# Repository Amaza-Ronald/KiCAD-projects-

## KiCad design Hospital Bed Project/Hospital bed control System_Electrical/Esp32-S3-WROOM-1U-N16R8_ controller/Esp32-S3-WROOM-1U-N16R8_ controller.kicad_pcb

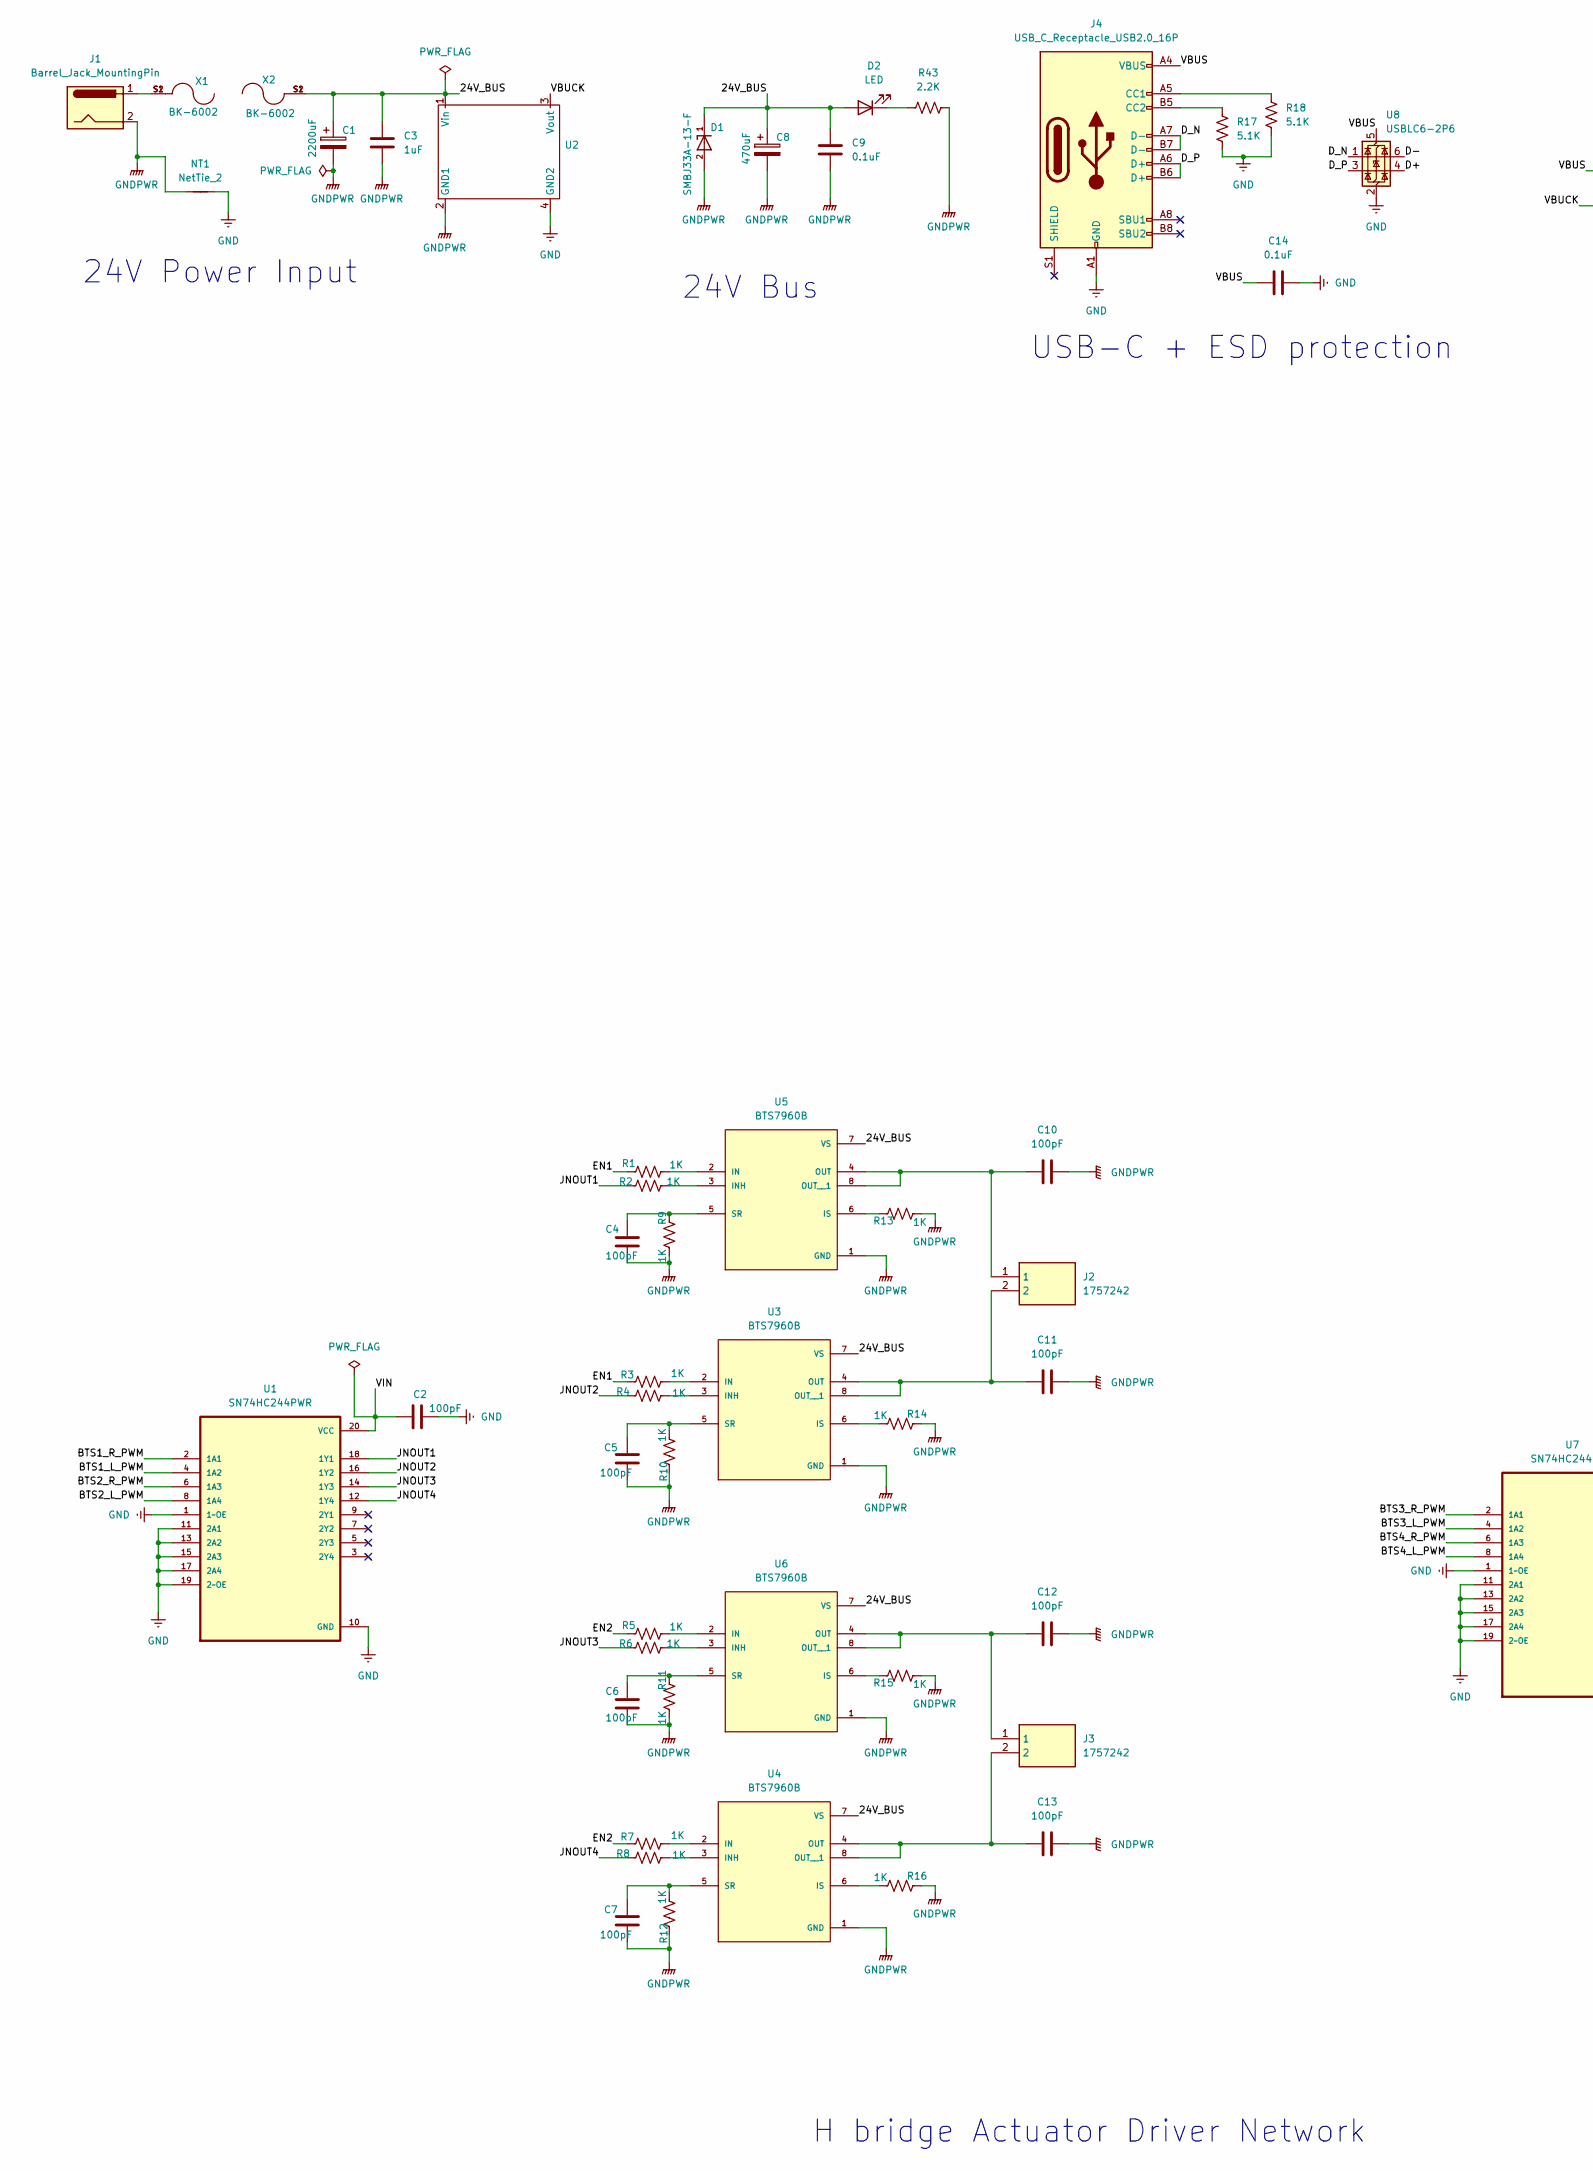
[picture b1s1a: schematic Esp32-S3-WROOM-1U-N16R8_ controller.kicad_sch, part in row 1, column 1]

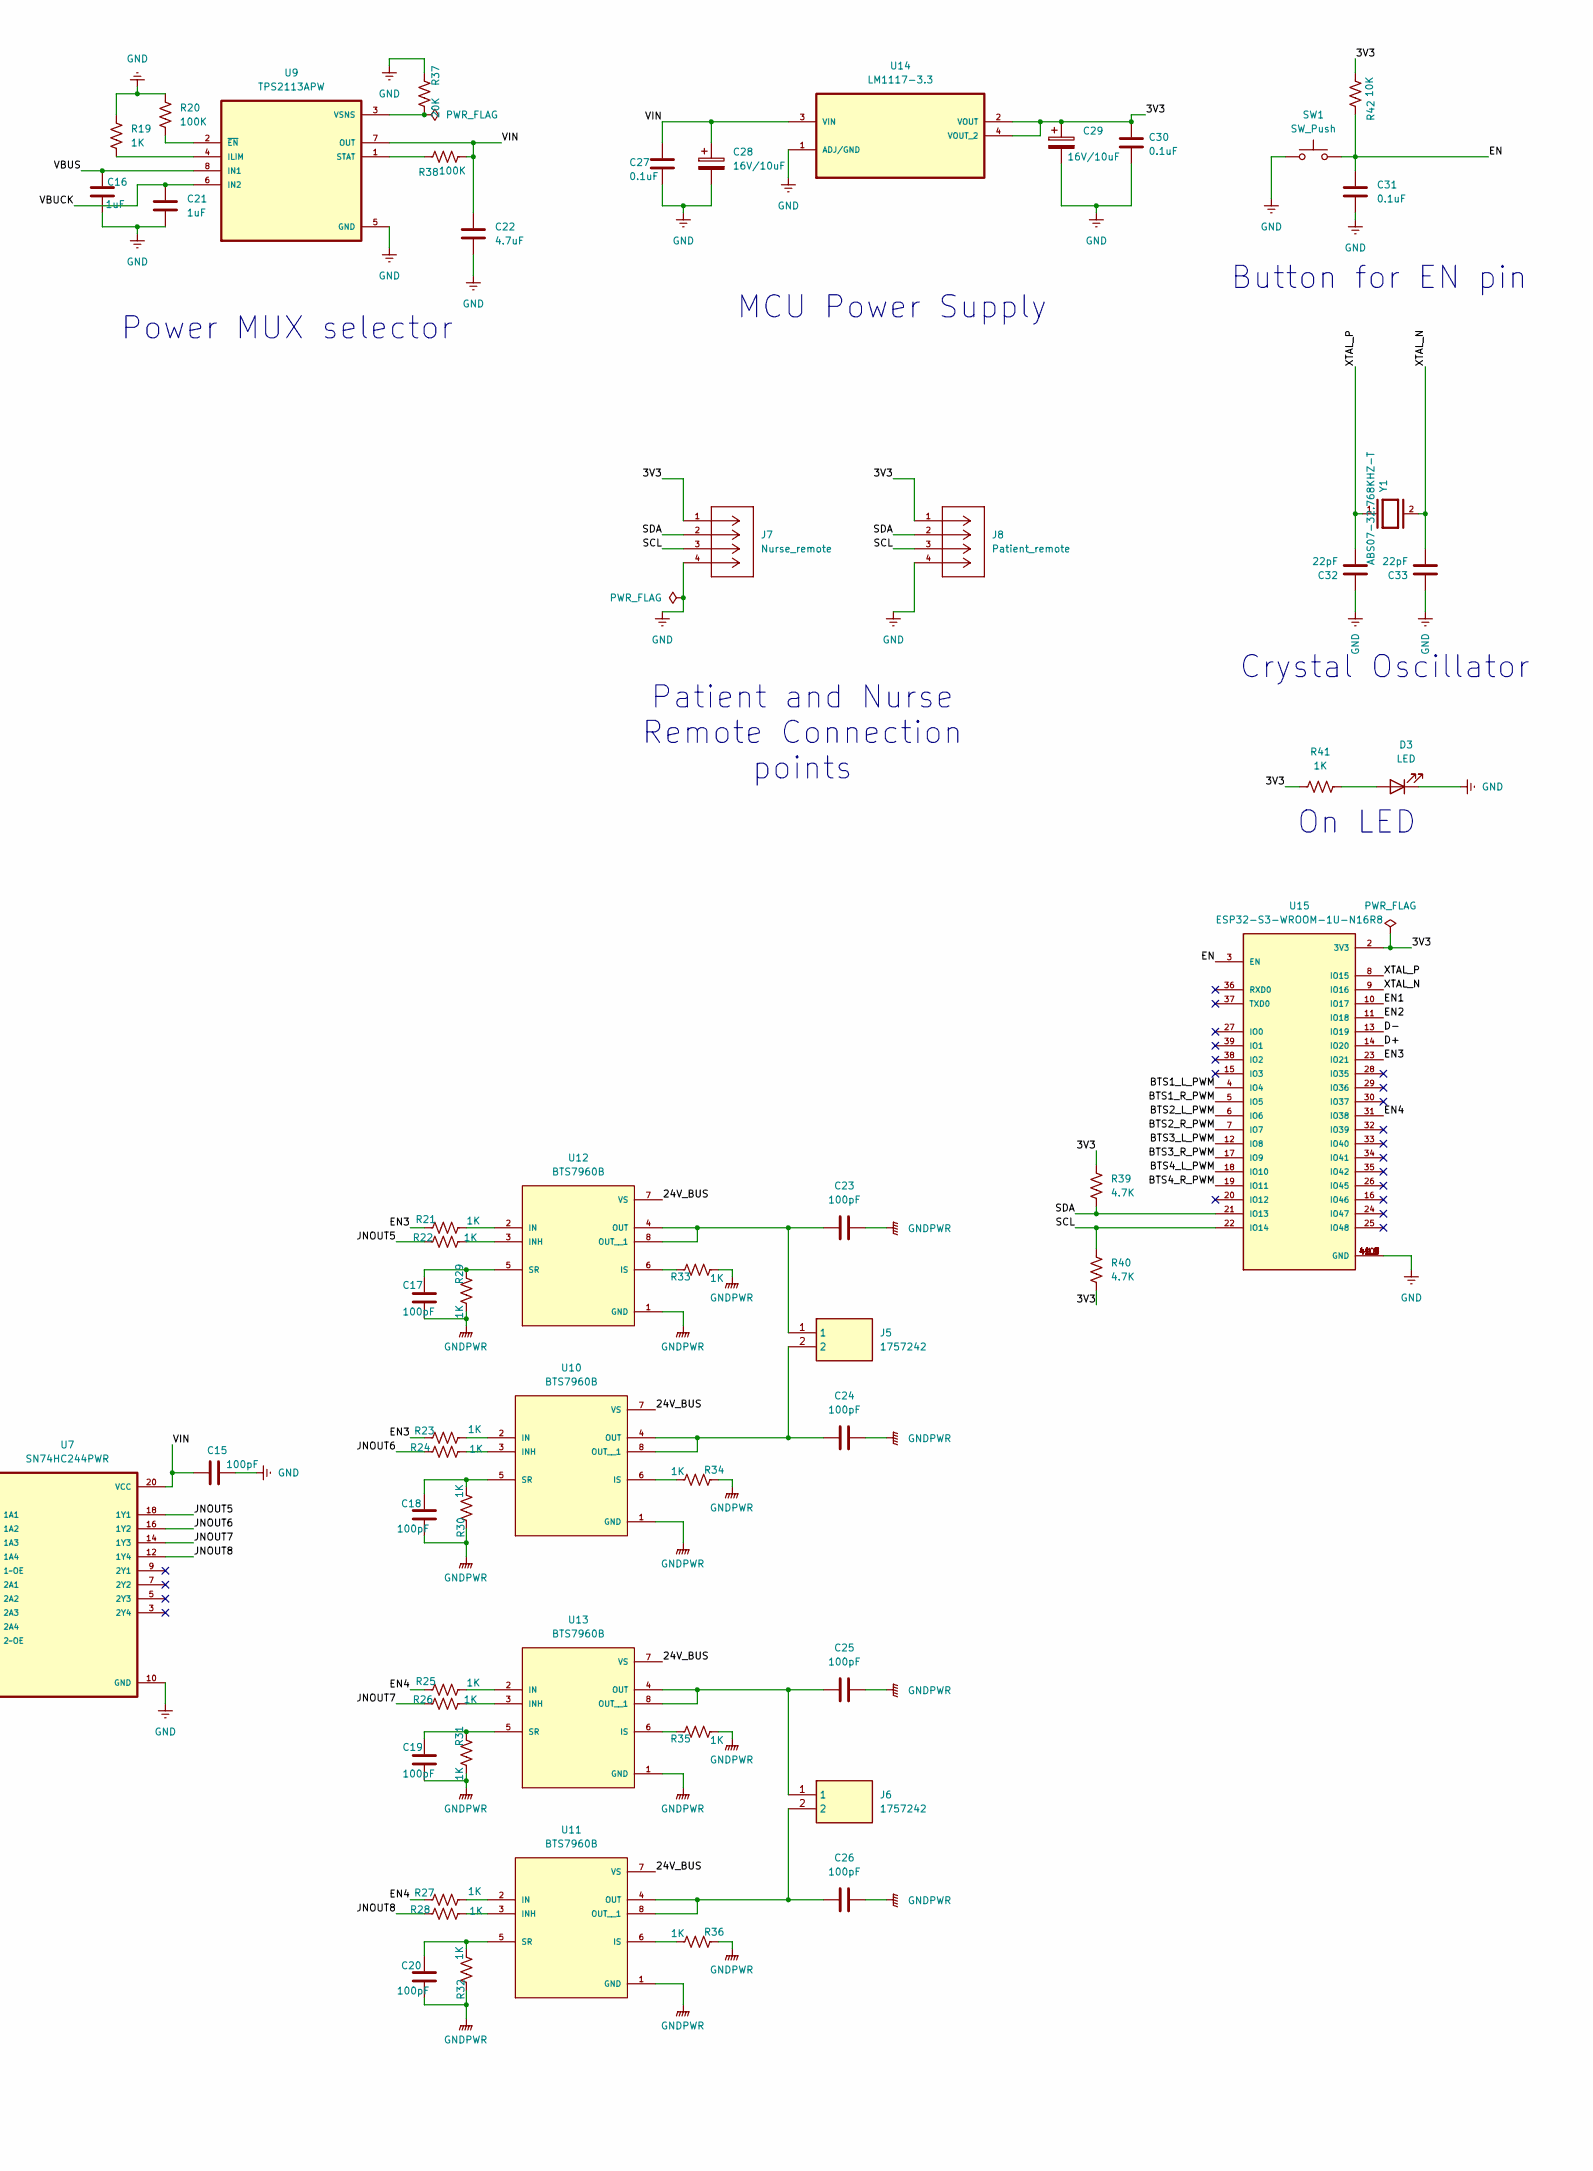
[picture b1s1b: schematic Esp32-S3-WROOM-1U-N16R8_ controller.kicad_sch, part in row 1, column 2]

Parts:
C1: 2200uF; CP_Radial_D16.0mm_P7.50mm
C2, C4, C5, C6, C7, C10, C11, C12, C13, C15, C17, C18, C19, C20, C23, C24, C25, C26: 100pF; C_0603_1608Metric
C3, C16, C21: 1uF; C_0603_1608Metric; MANUFACTURER_PART_NUMBER MAJCU168BB7104KTEA01
C8: 470uF; CP_Elec_10x10.5
C9, C14, C27, C30, C31: 0.1uF; C_0603_1608Metric; MANUFACTURER_PART_NUMBER MAJCU168BB7104KTEA01
C22: 4.7uF; C_0603_1608Metric; MANUFACTURER_PART_NUMBER 06036C475KAT2A
C28, C29: 16V/10uF; CP_Elec_4x5.4
C32, C33: 22pF; C_0603_1608Metric
D1: SMBJ33A-13-F; DIOM5336X250N; PARTREV 20 - 2
D2: LED; LED_D3.0mm
D3: LED; LED_1206_3216Metric
J1: Barrel_Jack_MountingPin; BarrelJack_GCT_DCJ200-10-A_Horizontal
J2, J3, J5, J6: 1757242; CONN_395224002_MOL; Mouser Part Number 651-1757242
J4: USB_C_Receptacle_USB2.0_16P; USB_C_Receptacle_GCT_USB4105-xx-A_16P_TopMnt_Horizontal
J7: Nurse_remote; CONN04_1718560004_MOL; MANUFACTURER_PART_NUMBER 1718560004
J8: Patient_remote; CONN04_1718560004_MOL; MANUFACTURER_PART_NUMBER 1718560004
NT1: NetTie_2; NetTie-2_SMD_Pad2.0mm
R1, R2, R3, R4, R5, R6, R7, R8, R9, R10, R11, R12, R13, R14, R15, R16, R19, R21, R22, R23, R24, R25, R26, R27, R28, R29, R30, R31, R32, R33, R34, R35, R36, R41: 1K; R_0603_1608Metric
R17, R18: 5.1K; R_0603_1608Metric
R20, R38: 100K; R_0603_1608Metric
R37: 20K; R_0603_1608Metric
R39, R40: 4.7K; R_0603_1608Metric
R42: 10K; R_0603_1608Metric
R43: 2.2K; R_0603_1608Metric
SW1: SW_Push; SW_SPST_FSMSM
U1, U7: SN74HC244PWR; SOP65P640X120-20N
U2: XL1509 DC-DC Step Down Buck Power Supply Module
U3, U4, U5, U6, U10, U11, U12, U13: BTS7960B; DPAK127P1490X440-8N; PARTREV 1.1
U8: USBLC6-2P6; SOT-666
U9: TPS2113APW; SOP65P640X120-8N; DigiKey_Part_Number 296-34596-5-ND
U14: LM1117-3.3; SOT230
U15: ESP32-S3-WROOM-1U-N16R8; XCVR_ESP32-S3-WROOM-1U-N16R8; PARTREV v1.1
X1, X2: BK-6002; BAT_BK-6002; PARTREV A
Y1: ABS07-32.768KHZ-T; XTAL_ABS07-32.768KHZ-T; PARTREV 08.19.15

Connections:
/3V3: C29.1, C30.2, J7.1, J8.1, R39.2, R40.1, R41.1, R42.2, U14.2 (VOUT), U14.4 (VOUT_2), U15.2 (3V3)
/24V_BUS: C1.1, C3.2, C8.1, C9.2, D1.1, D2.2 (A), U2.1 (Vin), U3.7 (VS), U4.7 (VS), U5.7 (VS), U6.7 (VS), U10.7 (VS), U11.7 (VS), U12.7 (VS), U13.7 (VS), X2.S1, X2.S2
/BTS1_L_PWM: U1.4 (1A2), U15.4 (IO4)
/BTS1_R_PWM: U1.2 (1A1), U15.5 (IO5)
/BTS2_L_PWM: U1.8 (1A4), U15.6 (IO6)
/BTS2_R_PWM: U1.6 (1A3), U15.7 (IO7)
/BTS3_L_PWM: U7.4 (1A2), U15.12 (IO8)
/BTS3_R_PWM: U7.2 (1A1), U15.17 (IO9)
/BTS4_L_PWM: U7.8 (1A4), U15.18 (IO10)
/BTS4_R_PWM: U7.6 (1A3), U15.19 (IO11)
/D+: U8.4 (I/O2), U15.14 (IO20)
/D-: U8.6 (I/O1), U15.13 (IO19)
/D_N: J4.A7 (D-), J4.B7 (D-), U8.1 (I/O1)
/D_P: J4.A6 (D+), J4.B6 (D+), U8.3 (I/O2)
/EN: C31.1, R42.1, SW1.2, U15.3 (EN)
/EN1: R1.1, R3.1, U15.10 (IO17)
/EN2: R5.1, R7.1, U15.11 (IO18)
/EN3: R21.1, R23.1, U15.23 (IO21)
/EN4: R25.1, R27.1, U15.31 (IO38)
/JNOUT1: R2.1, U1.18 (1Y1)
/JNOUT2: R4.1, U1.16 (1Y2)
/JNOUT3: R6.1, U1.14 (1Y3)
/JNOUT4: R8.1, U1.12 (1Y4)
/JNOUT5: R22.1, U7.18 (1Y1)
/JNOUT6: R24.1, U7.16 (1Y2)
/JNOUT7: R26.1, U7.14 (1Y3)
/JNOUT8: R28.1, U7.12 (1Y4)
/SCL: J7.3, J8.3, R40.2, U15.22 (IO14)
/SDA: J7.2, J8.2, R39.1, U15.21 (IO13)
/VBUCK: C21.2, U2.3 (Vout), U9.6 (IN2)
/VBUS: C14.1, C16.2, J4.A4 (VBUS), J4.A9 (VBUS), J4.B4 (VBUS), J4.B9 (VBUS), U8.5 (VBUS), U9.8 (IN1)
/VIN: C2.2, C15.2, C22.2, C27.2, C28.1, R38.2, U1.20 (VCC), U7.20 (VCC), U9.7 (OUT), U14.3 (VIN)
/XTAL_N: C33.1, U15.9 (IO16), Y1.2
/XTAL_P: C32.1, U15.8 (IO15), Y1.1
GND: C2.1, C14.2, C15.1, C16.1, C21.1, C22.1, C27.1, C28.2, C29.2, C30.1, C31.2, C32.2, C33.2, D3.1 (K), J4.A1 (GND), J4.A12 (GND), J4.B1 (GND), J4.B12 (GND), J7.4, J8.4, NT1.2, R17.2, R18.2, R19.1, R20.1, R37.2, SW1.1, U1.1 (1~OE), U1.10 (GND), U1.11 (2A1), U1.13 (2A2), U1.15 (2A3), U1.17 (2A4), U1.19 (2~OE), U2.4 (GND2), U7.1 (1~OE), U7.10 (GND), U7.11 (2A1), U7.13 (2A2), U7.15 (2A3), U7.17 (2A4), U7.19 (2~OE), U8.2 (GND), U9.5 (GND), U14.1 (ADJ/GND), U15.1 (GND), U15.40 (GND), U15.41_1 (GND), U15.41_2 (GND), U15.41_3 (GND), U15.41_4 (GND), U15.41_5 (GND), U15.41_6 (GND), U15.41_7 (GND), U15.41_8 (GND), U15.41_9 (GND)
GNDPWR: C1.2, C3.1, C4.2, C5.2, C6.2, C7.2, C8.2, C9.1, C10.2, C11.2, C12.2, C13.2, C17.2, C18.2, C19.2, C20.2, C23.2, C24.2, C25.2, C26.2, D1.2, J1.2, NT1.1, R9.1, R10.1, R11.1, R12.1, R13.1, R14.2, R15.1, R16.2, R29.1, R30.1, R31.1, R32.1, R33.1, R34.2, R35.1, R36.2, R43.2, U2.2 (GND1), U3.1 (GND), U4.1 (GND), U5.1 (GND), U6.1 (GND), U10.1 (GND), U11.1 (GND), U12.1 (GND), U13.1 (GND)
unnamed: D2.1 (K), R43.1
unnamed: D3.2 (A), R41.2
unnamed: J1.1, X1.S1, X1.S2
unnamed: J4.A5 (CC1), R18.1
unnamed: J4.B5 (CC2), R17.1
unnamed: R3.2, U3.2 (IN)
unnamed: R4.2, U3.3 (INH)
unnamed: R14.1, U3.6 (IS)
unnamed: C11.1, J2.2, U3.4 (OUT), U3.8 (OUT__1)
unnamed: C5.1, R10.2, U3.5 (SR)
unnamed: R7.2, U4.2 (IN)
unnamed: R8.2, U4.3 (INH)
unnamed: R16.1, U4.6 (IS)
unnamed: C13.1, J3.2, U4.4 (OUT), U4.8 (OUT__1)
unnamed: C7.1, R12.2, U4.5 (SR)
unnamed: R1.2, U5.2 (IN)
unnamed: R2.2, U5.3 (INH)
unnamed: R13.2, U5.6 (IS)
unnamed: C10.1, J2.1, U5.4 (OUT), U5.8 (OUT__1)
unnamed: C4.1, R9.2, U5.5 (SR)
unnamed: R5.2, U6.2 (IN)
unnamed: R6.2, U6.3 (INH)
unnamed: R15.2, U6.6 (IS)
unnamed: C12.1, J3.1, U6.4 (OUT), U6.8 (OUT__1)
unnamed: C6.1, R11.2, U6.5 (SR)
unnamed: R19.2, U9.4 (ILIM)
unnamed: R38.1, U9.1 (STAT)
unnamed: R37.1, U9.3 (VSNS)
unnamed: R20.2, U9.2 (~EN)
unnamed: R23.2, U10.2 (IN)
unnamed: R24.2, U10.3 (INH)
unnamed: R34.1, U10.6 (IS)
unnamed: C24.1, J5.2, U10.4 (OUT), U10.8 (OUT__1)
unnamed: C18.1, R30.2, U10.5 (SR)
unnamed: R27.2, U11.2 (IN)
unnamed: R28.2, U11.3 (INH)
unnamed: R36.1, U11.6 (IS)
unnamed: C26.1, J6.2, U11.4 (OUT), U11.8 (OUT__1)
unnamed: C20.1, R32.2, U11.5 (SR)
unnamed: R21.2, U12.2 (IN)
unnamed: R22.2, U12.3 (INH)
unnamed: R33.2, U12.6 (IS)
unnamed: C23.1, J5.1, U12.4 (OUT), U12.8 (OUT__1)
unnamed: C17.1, R29.2, U12.5 (SR)
unnamed: R25.2, U13.2 (IN)
unnamed: R26.2, U13.3 (INH)
unnamed: R35.2, U13.6 (IS)
unnamed: C25.1, J6.1, U13.4 (OUT), U13.8 (OUT__1)
unnamed: C19.1, R31.2, U13.5 (SR)

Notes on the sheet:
H bridge Actuator Driver Network
Crystal Oscillator
MCU Power Supply
Power MUX selector
24V Bus
Button for EN pin
USB-C + ESD protection
24V Power Input
On LED
Patient and Nurse Remote Connection points

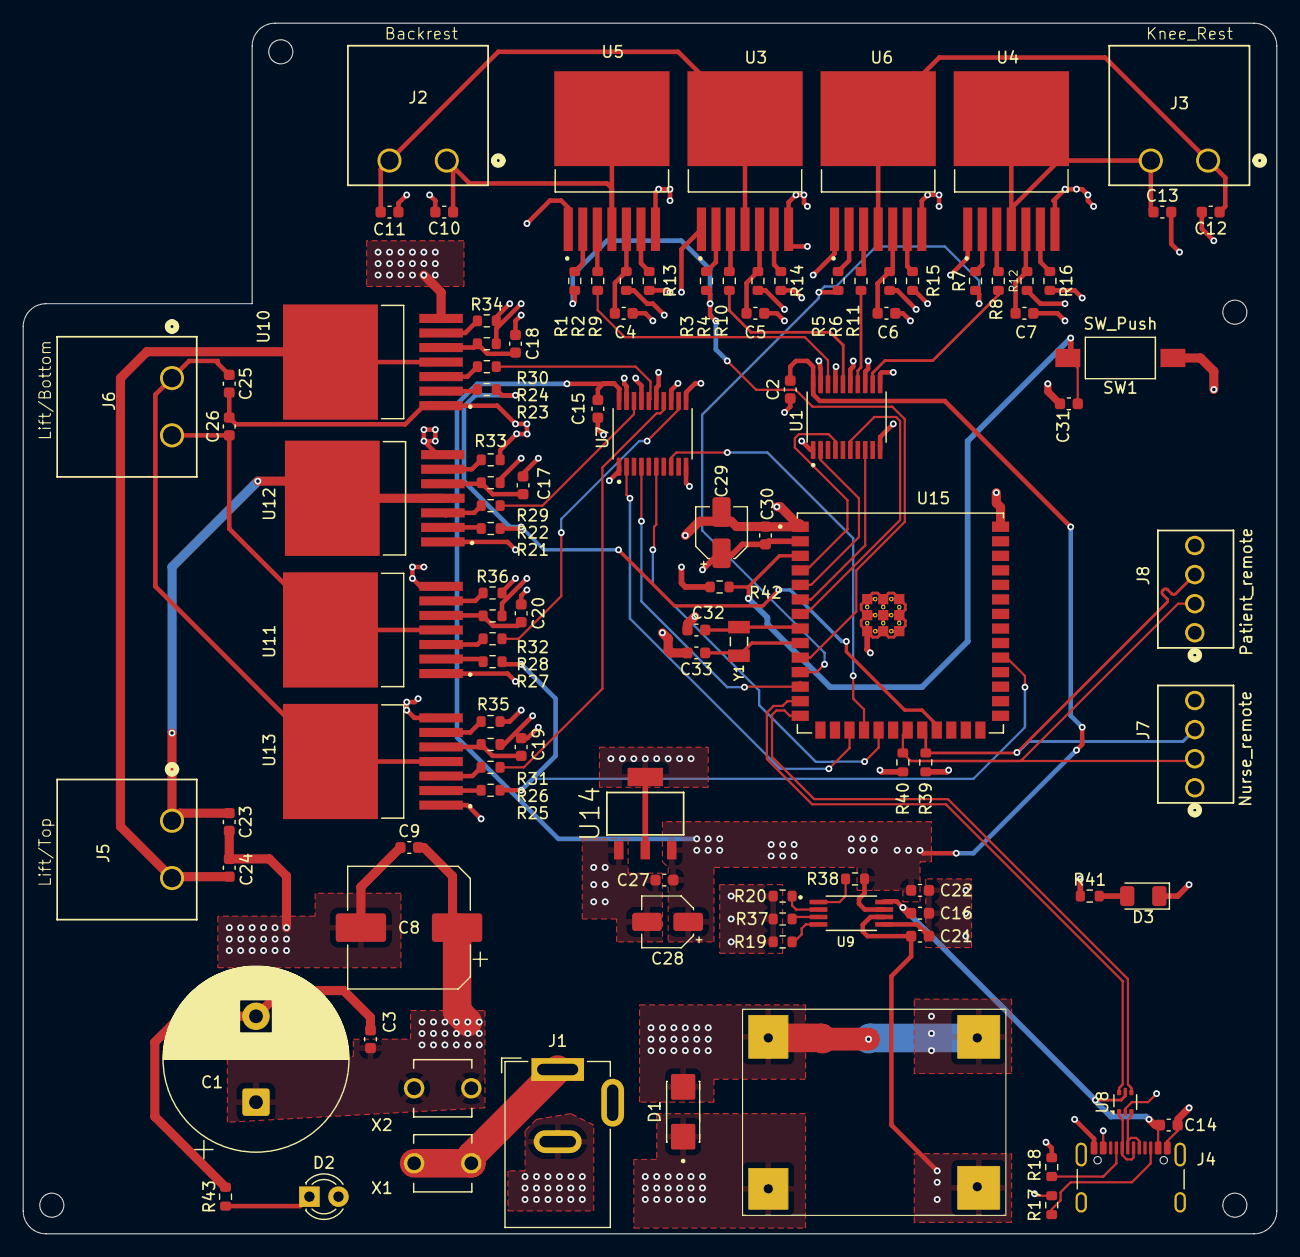
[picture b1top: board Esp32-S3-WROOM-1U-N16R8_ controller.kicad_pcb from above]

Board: 4 copper layers, 109.5 x 105.7 mm, 111 parts (0 on the bottom side), 85 nets.

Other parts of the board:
REF2, REF2#2, REF3, REF4: MountingHole_2.1mm

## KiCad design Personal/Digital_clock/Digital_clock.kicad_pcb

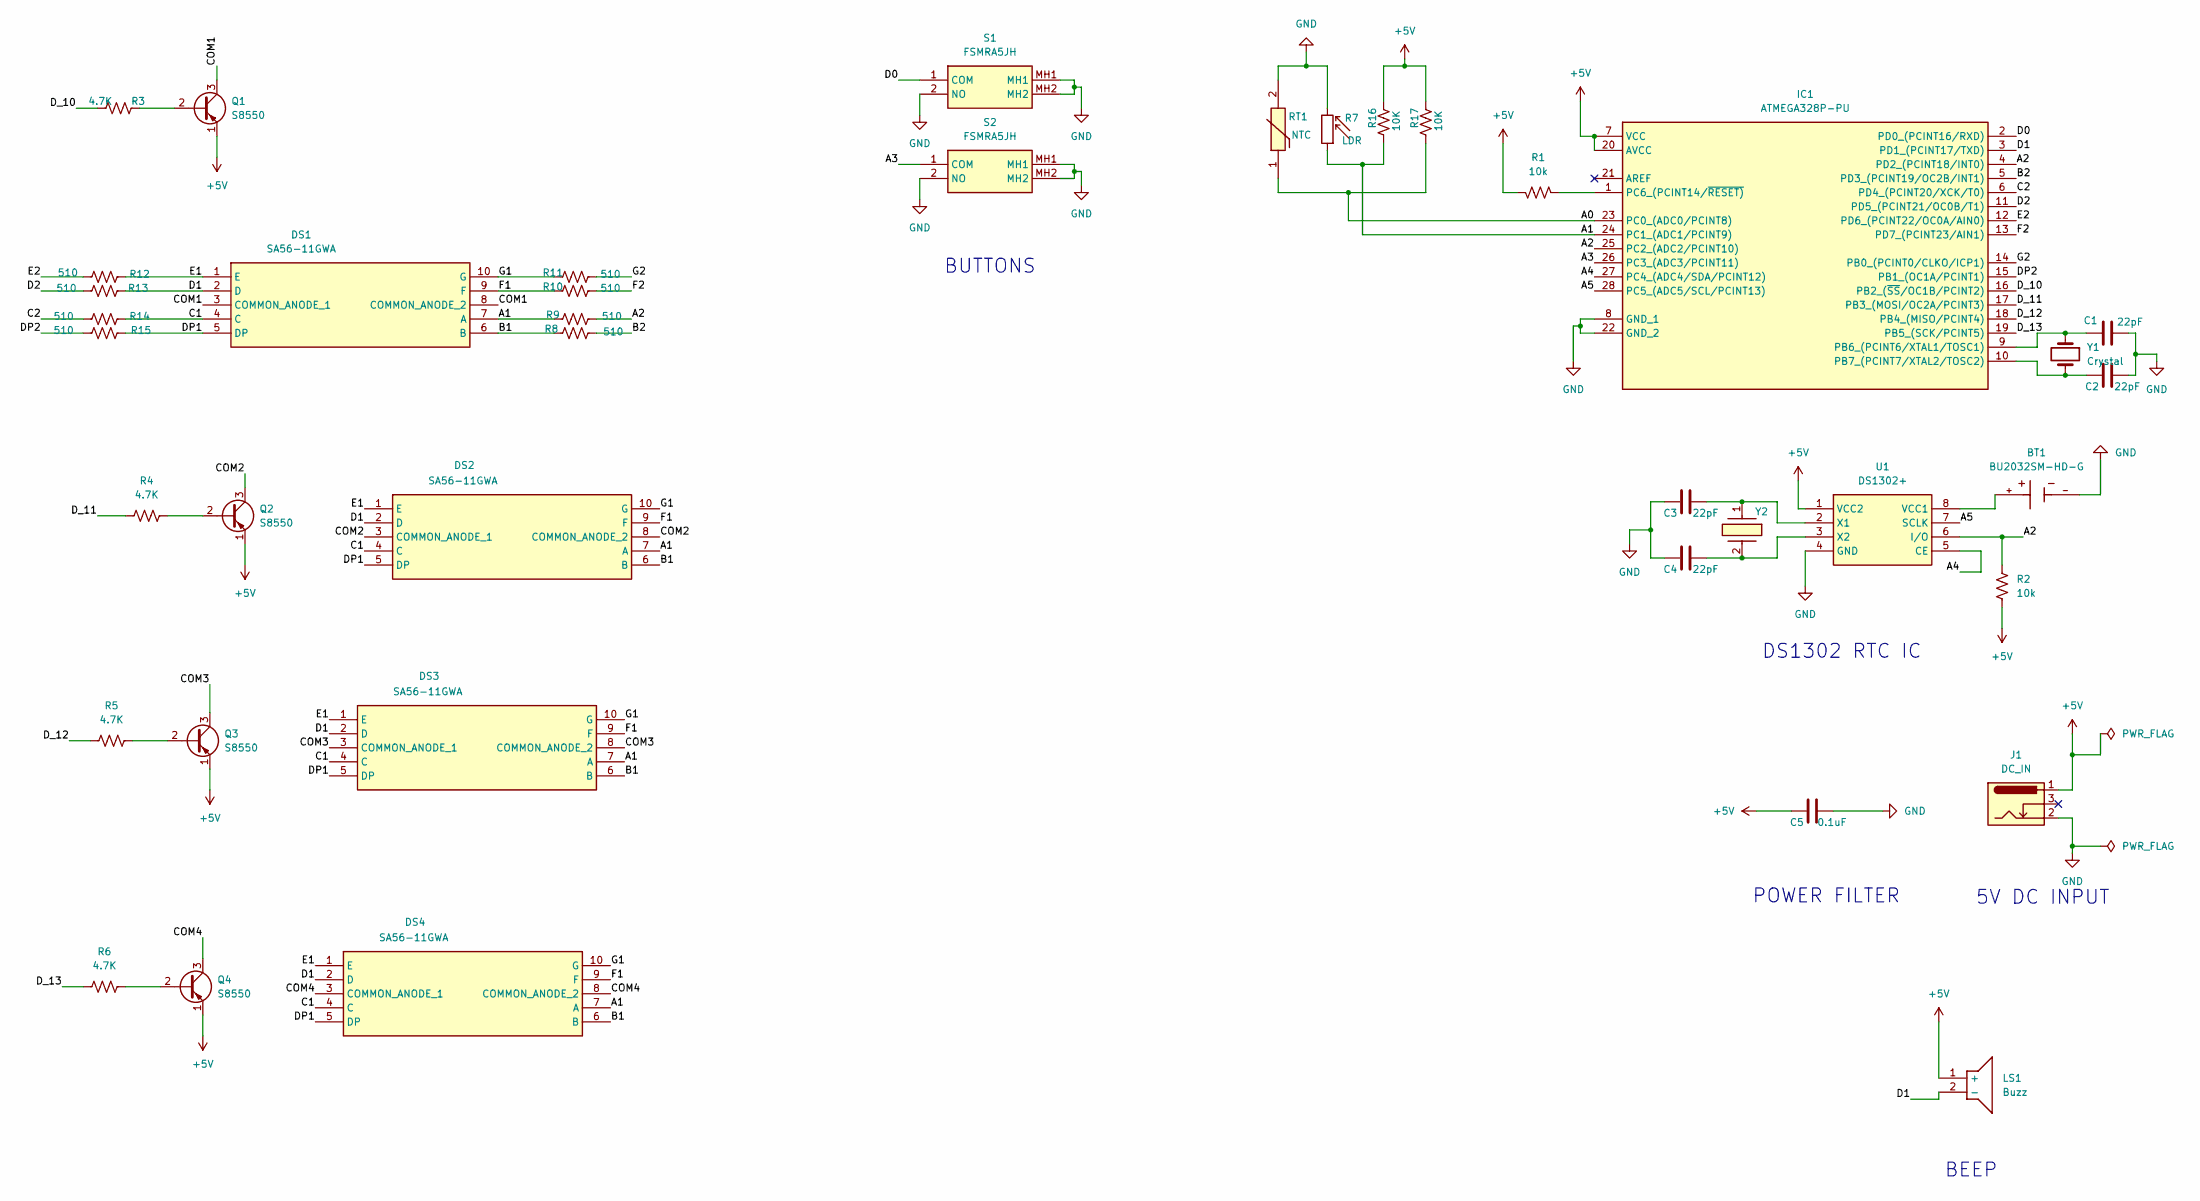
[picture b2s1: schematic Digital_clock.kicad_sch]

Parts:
BT1: BU2032SM-HD-G; BAT_BU2032SM-HD-G; PARTREV 01/27/17
C1, C2, C3, C4: 22pF; C_Disc_D5.0mm_W2.5mm_P2.50mm
C5: 0.1uF; C_Disc_D5.0mm_W2.5mm_P2.50mm
DS1, DS2, DS3, DS4: SA56-11GWA; DIP3040W75P254L2400H1050Q10N; Manufacturer_Part_Number SA10-21SURKWA; Mouser Part Number 604-SA56-11GWA
IC1: ATMEGA328P-PU; DIP794W53P254L3467H457Q28N; Manufacturer_Part_Number ATMEGA328P-PU; Mouser Part Number 556-ATMEGA328P-PU
J1: DC_IN; BarrelJack_Horizontal
LS1: Buzz; ABT410RC; Manufacturer_Part_Number ABT-410-RC
Q1, Q2, Q3, Q4: S8550; TO-92_Inline
R1, R2: 10k; R_Axial_DIN0207_L6.3mm_D2.5mm_P10.16mm_Horizontal
R3, R4, R5, R6: 4.7K; R_Axial_DIN0207_L6.3mm_D2.5mm_P10.16mm_Horizontal
R7: LDR; R_LDR_10x8.5mm_P7.6mm_Vertical
R8, R9, R10, R11, R12, R13, R14, R15: 510; R_Axial_DIN0207_L6.3mm_D2.5mm_P10.16mm_Horizontal
R16, R17: 10K; R_Axial_DIN0207_L6.3mm_D2.5mm_P10.16mm_Horizontal
RT1: NTC; NTCLE100E3103JB0; Mouser Part Number 594-2381-640-63103
S1, S2: FSMRA5JH; FSMRA5JH04; Manufacturer_Part_Number FSMRA5JH04; Mouser Part Number 506-1-1825027-4
U1: DS1302+; DIP762W56P254L938H457Q8N; Manufacturer_Part_Number DS1302N+; Mouser Part Number 700-DS1302N
Y1: Crystal; Crystal_HC49-4H_Vertical
Y2: AB38T-32.768KHZ; AB38T32768KHZ; Manufacturer_Part_Number AB38T-32.768KHZ; Mouser Part Number 815-AB38T-32.768KHZ

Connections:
+5V: C5.1, IC1.7 (VCC), IC1.20 (AVCC), J1.1, LS1.1 (+), Q1.1 (E), Q2.1 (E), Q3.1 (E), Q4.1 (E), R1.2, R2.1, R16.2, R17.2, U1.1 (VCC2)
/A0: IC1.23 (PC0_(ADC0/PCINT8)), R17.1, RT1.1
/A1: DS1.7 (A), DS2.7 (A), DS3.7 (A), DS4.7 (A), IC1.24 (PC1_(ADC1/PCINT9)), R7.1, R9.1, R16.1
/A2: IC1.4 (PD2_(PCINT18/INT0)), IC1.25 (PC2_(ADC2/PCINT10)), R2.2, R9.2, U1.6 (I/O)
/A3: IC1.26 (PC3_(ADC3/PCINT11)), S2.1 (COM)
/A4: IC1.27 (PC4_(ADC4/SDA/PCINT12)), U1.5 (CE)
/A5: IC1.28 (PC5_(ADC5/SCL/PCINT13)), U1.7 (SCLK)
/B1: DS1.6 (B), DS2.6 (B), DS3.6 (B), DS4.6 (B), R8.1
/B2: IC1.5 (PD3_(PCINT19/OC2B/INT1)), R8.2
/C1: DS1.4 (C), DS2.4 (C), DS3.4 (C), DS4.4 (C), R14.2
/C2: IC1.6 (PD4_(PCINT20/XCK/T0)), R14.1
/COM1: DS1.3 (COMMON_ANODE_1), DS1.8 (COMMON_ANODE_2), Q1.3 (C)
/COM2: DS2.3 (COMMON_ANODE_1), DS2.8 (COMMON_ANODE_2), Q2.3 (C)
/COM3: DS3.3 (COMMON_ANODE_1), DS3.8 (COMMON_ANODE_2), Q3.3 (C)
/COM4: DS4.3 (COMMON_ANODE_1), DS4.8 (COMMON_ANODE_2), Q4.3 (C)
/D0: IC1.2 (PD0_(PCINT16/RXD)), S1.1 (COM)
/D1: DS1.2 (D), DS2.2 (D), DS3.2 (D), DS4.2 (D), IC1.3 (PD1_(PCINT17/TXD)), LS1.2 (-), R13.2
/D2: IC1.11 (PD5_(PCINT21/OC0B/T1)), R13.1
/DP1: DS1.5 (DP), DS2.5 (DP), DS3.5 (DP), DS4.5 (DP), R15.2
/DP2: IC1.15 (PB1_(OC1A/PCINT1)), R15.1
/D_10: IC1.16 (PB2_(~SS/OC1B/PCINT2)), R3.1
/D_11: IC1.17 (PB3_(MOSI/OC2A/PCINT3)), R4.1
/D_12: IC1.18 (PB4_(MISO/PCINT4)), R5.1
/D_13: IC1.19 (PB5_(SCK/PCINT5)), R6.1
/E1: DS1.1 (E), DS2.1 (E), DS3.1 (E), DS4.1 (E), R12.2
/E2: IC1.12 (PD6_(PCINT22/OC0A/AIN0)), R12.1
/F1: DS1.9 (F), DS2.9 (F), DS3.9 (F), DS4.9 (F), R10.1
/F2: IC1.13 (PD7_(PCINT23/AIN1)), R10.2
/G1: DS1.10 (G), DS2.10 (G), DS3.10 (G), DS4.10 (G), R11.1
/G2: IC1.14 (PB0_(PCINT0/CLKO/ICP1)), R11.2
GND: BT1.-, C1.2, C2.2, C3.1, C4.1, C5.2, IC1.8 (GND_1), IC1.22 (GND_2), J1.2, R7.2, RT1.2, S1.2 (NO), S1.MH1, S1.MH2, S2.2 (NO), S2.MH1, S2.MH2, U1.4 (GND); also elsewhere on the board
unnamed: C1.1, IC1.9 (PB6_(PCINT6/XTAL1/TOSC1)), Y1.1
unnamed: C2.1, IC1.10 (PB7_(PCINT7/XTAL2/TOSC2)), Y1.2
unnamed: IC1.1 (PC6_(PCINT14/~RESET)), R1.1
unnamed: Q1.2 (B), R3.2
unnamed: Q2.2 (B), R4.2
unnamed: Q3.2 (B), R5.2
unnamed: Q4.2 (B), R6.2
unnamed 38: BT1.+, U1.8 (VCC1); also elsewhere on the board
unnamed: C3.2, U1.2 (X1), Y2.1
unnamed: C4.2, U1.3 (X2), Y2.2

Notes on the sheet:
5V DC INPUT
BUTTONS
BEEP
POWER FILTER
DS1302 RTC IC

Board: 2 copper layers, 41 parts (0 on the bottom side), 41 nets, no tracks yet.

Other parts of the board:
BAT1: BU2032SM-JJ-GTR; BAT_BU2032SM-JJ-GTR

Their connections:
GND: BAT1.-; also elsewhere on the board
unnamed 38: BAT1.+; also elsewhere on the board

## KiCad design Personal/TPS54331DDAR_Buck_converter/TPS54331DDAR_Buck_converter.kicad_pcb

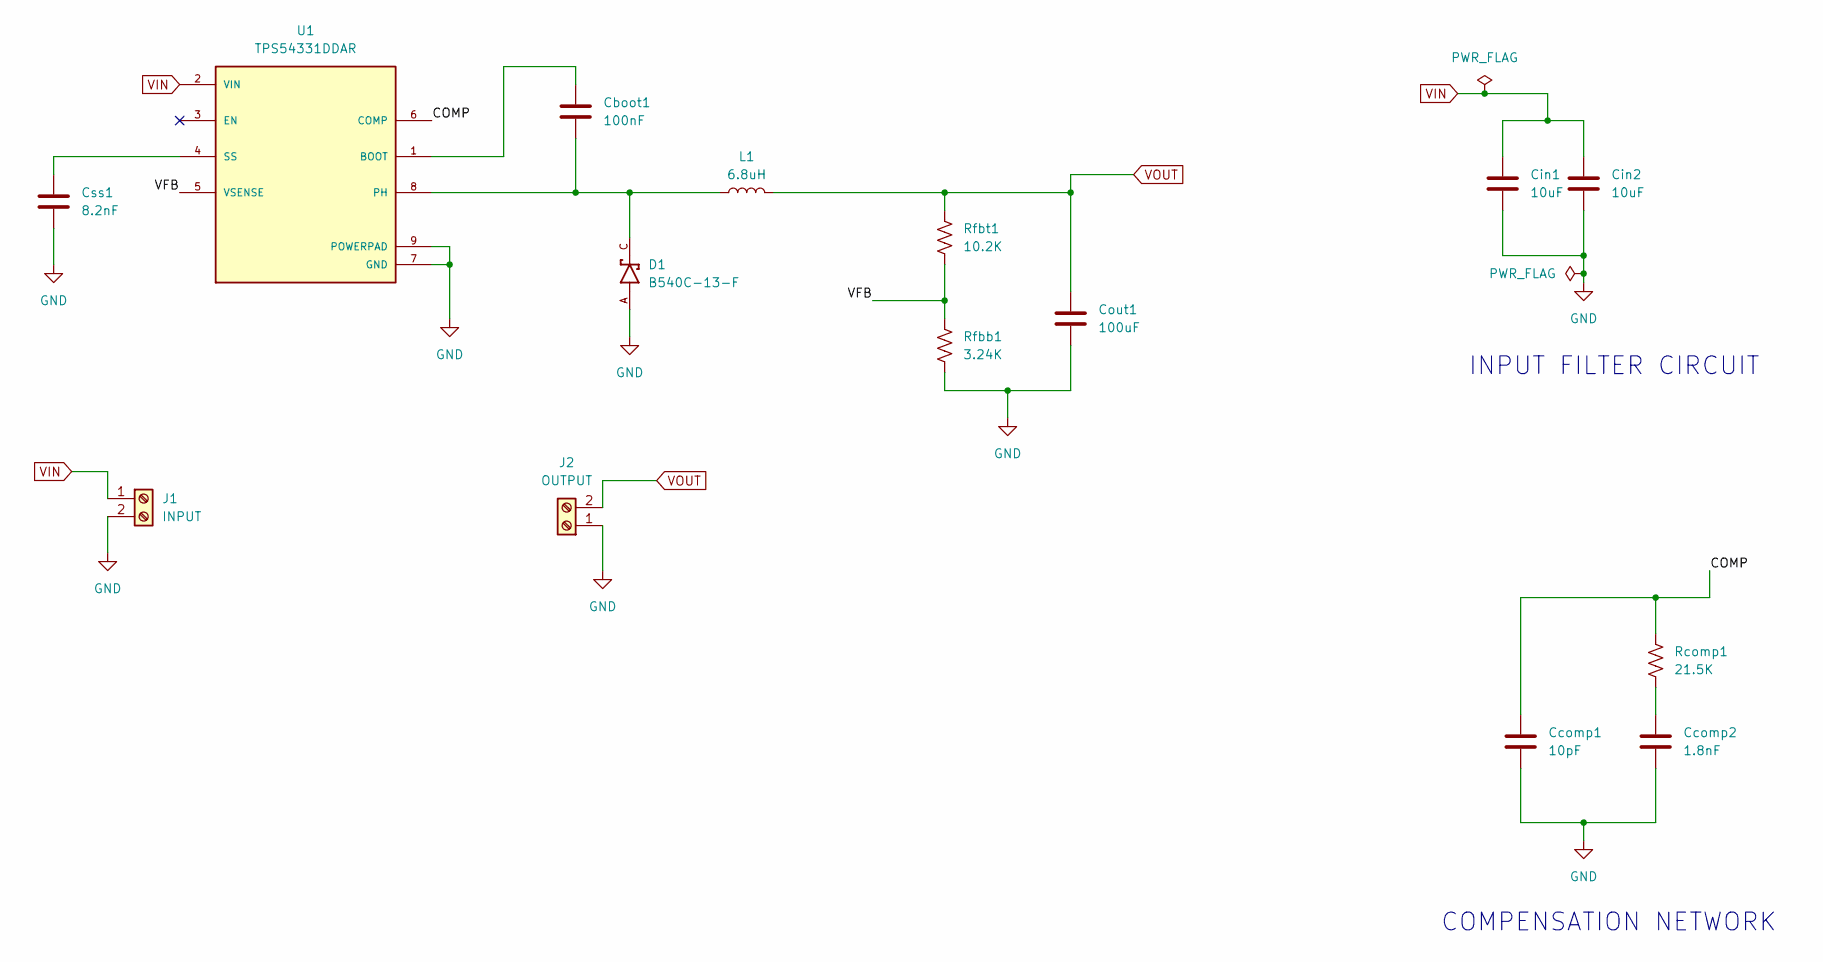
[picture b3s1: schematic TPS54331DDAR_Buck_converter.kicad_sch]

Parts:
Cboot1: 100nF; C_0402_1005Metric
Ccomp1: 10pF; C_0805_2012Metric
Ccomp2: 1.8nF; C_0805_2012Metric
Cin1, Cin2: 10uF; C_1210_3225Metric
Cout1: 100uF; C_1210_3225Metric
Css1: 8.2nF; C_0201_0603Metric
D1: B540C-13-F; DIOM6959X245N; PARTREV V1.0
J1: INPUT; 19774772
J2: OUTPUT; 19774772
L1: 6.8uH; XAL5020801MEC
Rcomp1: 21.5K; C_0402_1005Metric
Rfbb1: 3.24K; C_0402_1005Metric
Rfbt1: 10.2K; C_0402_1005Metric
U1: TPS54331DDAR; CONV_TPS54331DDAR; PARTREV F

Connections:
/COMP: Ccomp1.1, Rcomp1.1, U1.6 (COMP)
/VFB: Rfbb1.1, Rfbt1.2, U1.5 (VSENSE)
GND: Ccomp1.2, Ccomp2.2, Cin1.2, Cin2.2, Cout1.2, Css1.2, D1.A, J1.2, J2.1, Rfbb1.2, U1.7 (GND), U1.9 (POWERPAD)
unnamed: Ccomp2.1, Rcomp1.2
unnamed: Cboot1.2, U1.1 (BOOT)
unnamed: Cboot1.1, D1.C, L1.1, U1.8 (PH)
unnamed: Css1.1, U1.4 (SS)
VIN: Cin1.1, Cin2.1, J1.1, U1.2 (VIN)
VOUT: Cout1.1, J2.2, L1.2, Rfbt1.1

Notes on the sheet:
INPUT FILTER CIRCUIT
COMPENSATION NETWORK

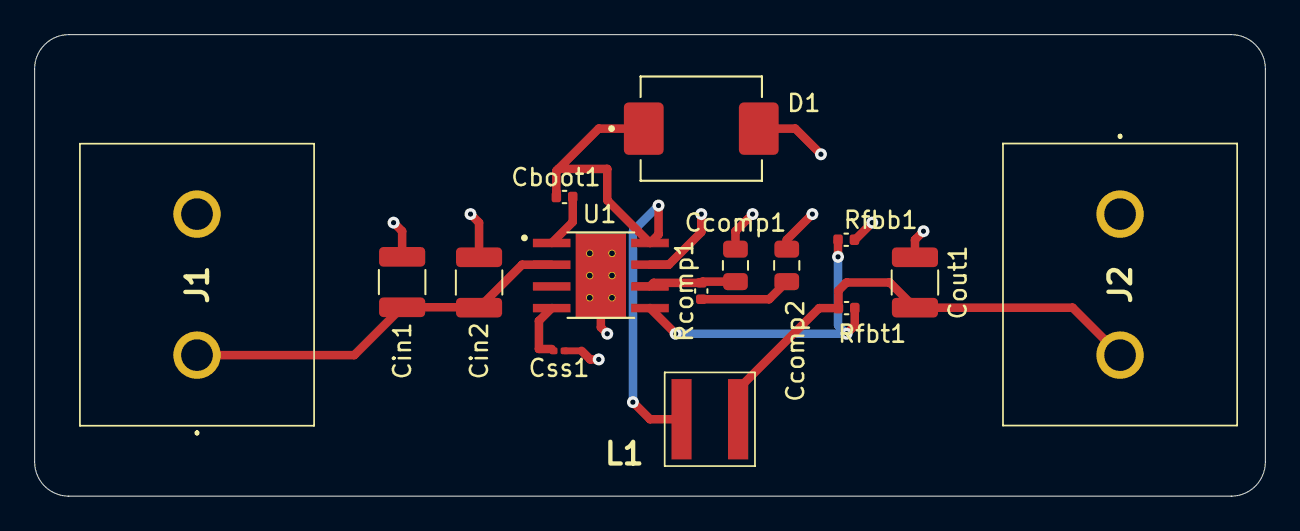
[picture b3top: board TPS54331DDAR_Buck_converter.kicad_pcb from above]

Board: 2 copper layers, 72.0 x 27.0 mm, 15 parts (0 on the bottom side), 9 nets.
